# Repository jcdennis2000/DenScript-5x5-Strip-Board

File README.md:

# DenScript-5x5-Strip-Board

You’ve probably heard of prototyping boards, but what are Strip Boards?

A Strip Board is just like a prototyping board, except the pads are connected in tracks, meaning you can more easily make circuits! Using a small hand drill (sold separately), you can cut the tracks, and using wires you can connect tracks.

Perfect for projects that you need to prototype quickly, in a DenBlock format, complete with M4 mounting holes in each corner so you can easily attach your prototype to your projects!

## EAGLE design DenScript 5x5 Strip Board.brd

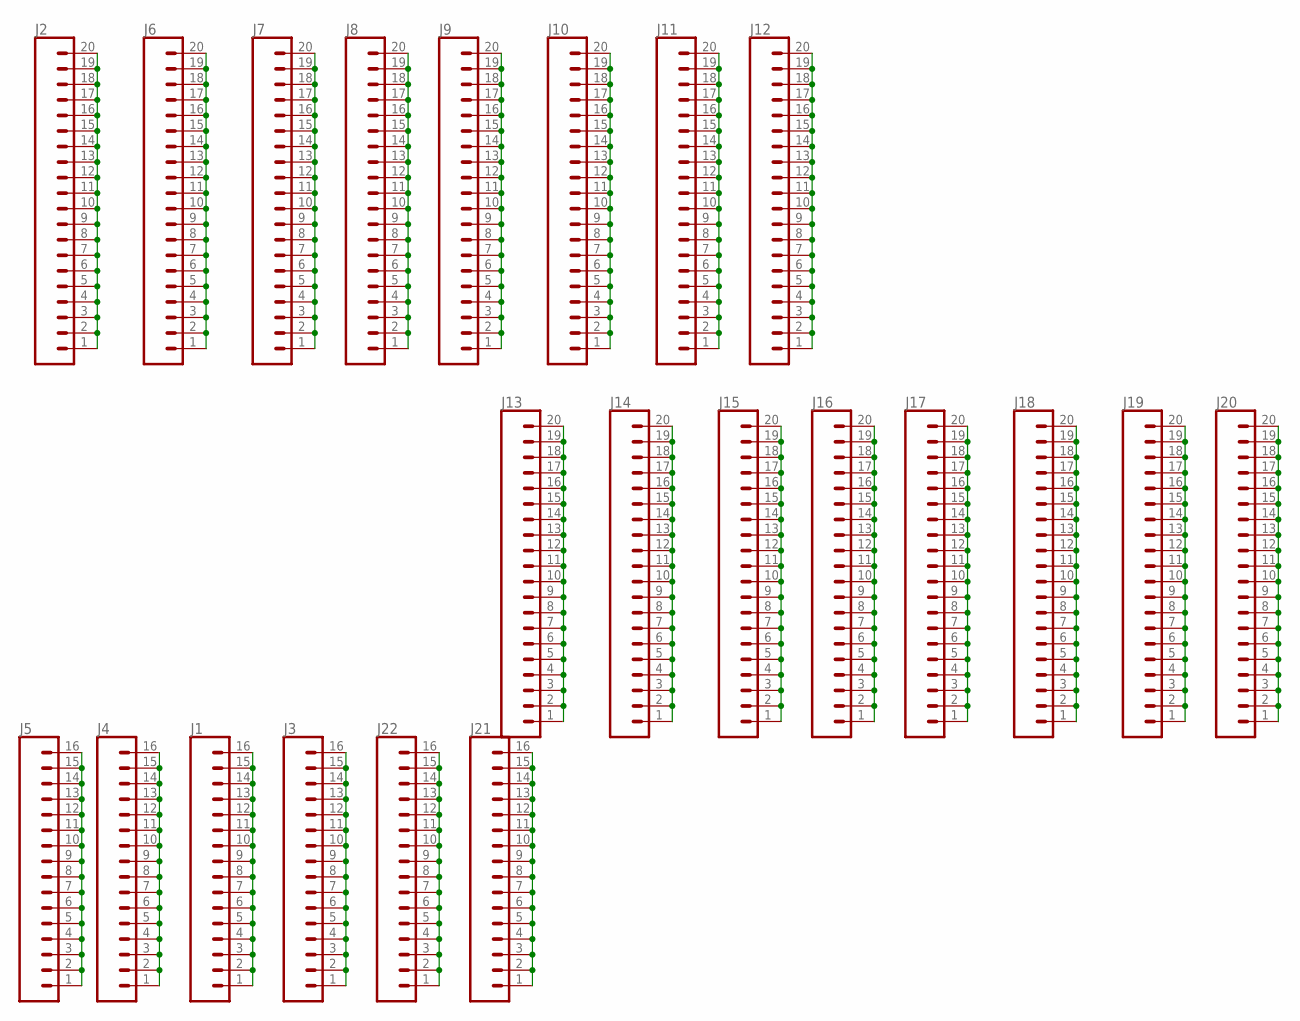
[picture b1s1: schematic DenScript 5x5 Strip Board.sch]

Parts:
J1, J3, J4, J5, J21, J22: CONN_161X16_NO_SILK; 1X16_NO_SILK
J2, J6, J7, J8, J9, J10, J11, J12, J13, J14, J15, J16, J17, J18, J19, J20: CONN_20NOSILK; 1X20_NOSILK

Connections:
unnamed: J3.1, J3.2, J3.3, J3.4, J3.5, J3.6, J3.7, J3.8, J3.9, J3.10, J3.11, J3.12, J3.13, J3.14, J3.15, J3.16
unnamed: J1.1, J1.2, J1.3, J1.4, J1.5, J1.6, J1.7, J1.8, J1.9, J1.10, J1.11, J1.12, J1.13, J1.14, J1.15, J1.16
unnamed: J4.1, J4.2, J4.3, J4.4, J4.5, J4.6, J4.7, J4.8, J4.9, J4.10, J4.11, J4.12, J4.13, J4.14, J4.15, J4.16
unnamed: J5.1, J5.2, J5.3, J5.4, J5.5, J5.6, J5.7, J5.8, J5.9, J5.10, J5.11, J5.12, J5.13, J5.14, J5.15, J5.16
unnamed: J2.1, J2.2, J2.3, J2.4, J2.5, J2.6, J2.7, J2.8, J2.9, J2.10, J2.11, J2.12, J2.13, J2.14, J2.15, J2.16, J2.17, J2.18, J2.19, J2.20
unnamed: J6.1, J6.2, J6.3, J6.4, J6.5, J6.6, J6.7, J6.8, J6.9, J6.10, J6.11, J6.12, J6.13, J6.14, J6.15, J6.16, J6.17, J6.18, J6.19, J6.20
unnamed: J7.1, J7.2, J7.3, J7.4, J7.5, J7.6, J7.7, J7.8, J7.9, J7.10, J7.11, J7.12, J7.13, J7.14, J7.15, J7.16, J7.17, J7.18, J7.19, J7.20
unnamed: J8.1, J8.2, J8.3, J8.4, J8.5, J8.6, J8.7, J8.8, J8.9, J8.10, J8.11, J8.12, J8.13, J8.14, J8.15, J8.16, J8.17, J8.18, J8.19, J8.20
unnamed: J9.1, J9.2, J9.3, J9.4, J9.5, J9.6, J9.7, J9.8, J9.9, J9.10, J9.11, J9.12, J9.13, J9.14, J9.15, J9.16, J9.17, J9.18, J9.19, J9.20
unnamed: J10.1, J10.2, J10.3, J10.4, J10.5, J10.6, J10.7, J10.8, J10.9, J10.10, J10.11, J10.12, J10.13, J10.14, J10.15, J10.16, J10.17, J10.18, J10.19, J10.20
unnamed: J11.1, J11.2, J11.3, J11.4, J11.5, J11.6, J11.7, J11.8, J11.9, J11.10, J11.11, J11.12, J11.13, J11.14, J11.15, J11.16, J11.17, J11.18, J11.19, J11.20
unnamed: J12.1, J12.2, J12.3, J12.4, J12.5, J12.6, J12.7, J12.8, J12.9, J12.10, J12.11, J12.12, J12.13, J12.14, J12.15, J12.16, J12.17, J12.18, J12.19, J12.20
unnamed: J13.1, J13.2, J13.3, J13.4, J13.5, J13.6, J13.7, J13.8, J13.9, J13.10, J13.11, J13.12, J13.13, J13.14, J13.15, J13.16, J13.17, J13.18, J13.19, J13.20
unnamed: J14.1, J14.2, J14.3, J14.4, J14.5, J14.6, J14.7, J14.8, J14.9, J14.10, J14.11, J14.12, J14.13, J14.14, J14.15, J14.16, J14.17, J14.18, J14.19, J14.20
unnamed: J15.1, J15.2, J15.3, J15.4, J15.5, J15.6, J15.7, J15.8, J15.9, J15.10, J15.11, J15.12, J15.13, J15.14, J15.15, J15.16, J15.17, J15.18, J15.19, J15.20
unnamed: J16.1, J16.2, J16.3, J16.4, J16.5, J16.6, J16.7, J16.8, J16.9, J16.10, J16.11, J16.12, J16.13, J16.14, J16.15, J16.16, J16.17, J16.18, J16.19, J16.20
unnamed: J17.1, J17.2, J17.3, J17.4, J17.5, J17.6, J17.7, J17.8, J17.9, J17.10, J17.11, J17.12, J17.13, J17.14, J17.15, J17.16, J17.17, J17.18, J17.19, J17.20
unnamed: J18.1, J18.2, J18.3, J18.4, J18.5, J18.6, J18.7, J18.8, J18.9, J18.10, J18.11, J18.12, J18.13, J18.14, J18.15, J18.16, J18.17, J18.18, J18.19, J18.20
unnamed: J19.1, J19.2, J19.3, J19.4, J19.5, J19.6, J19.7, J19.8, J19.9, J19.10, J19.11, J19.12, J19.13, J19.14, J19.15, J19.16, J19.17, J19.18, J19.19, J19.20
unnamed: J20.1, J20.2, J20.3, J20.4, J20.5, J20.6, J20.7, J20.8, J20.9, J20.10, J20.11, J20.12, J20.13, J20.14, J20.15, J20.16, J20.17, J20.18, J20.19, J20.20
unnamed: J21.1, J21.2, J21.3, J21.4, J21.5, J21.6, J21.7, J21.8, J21.9, J21.10, J21.11, J21.12, J21.13, J21.14, J21.15, J21.16
unnamed: J22.1, J22.2, J22.3, J22.4, J22.5, J22.6, J22.7, J22.8, J22.9, J22.10, J22.11, J22.12, J22.13, J22.14, J22.15, J22.16

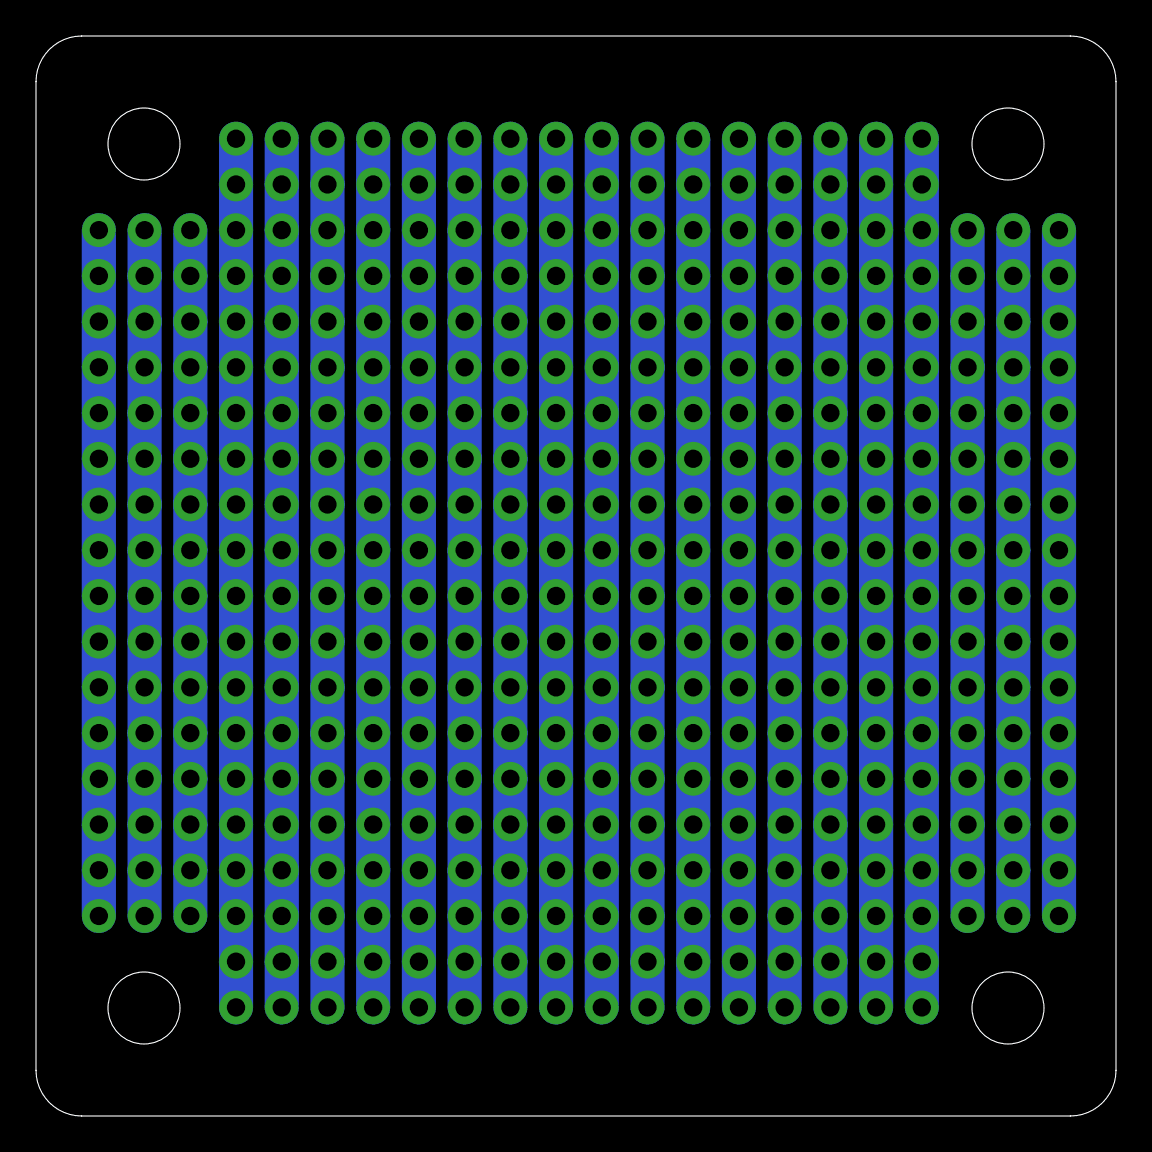
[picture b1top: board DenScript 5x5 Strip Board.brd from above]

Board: 2 copper layers, 60.0 x 60.0 mm, 22 parts (0 on the bottom side), 22 nets.

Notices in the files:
parts and their libraries:
SparkFun-Connectors: Licensing: Creative Commons ShareAlike 4.0 International - https://creativecommons.org/licenses/by-sa/4.0
